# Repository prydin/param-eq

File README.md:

# Parametric EQ to DSP Playground

This project started as a focused experiment: build a practical, hardware-controlled parametric equalizer.
Along the way it grew into something broader: a general-purpose DSP platform for real-time audio processing,
instrumentation, and UI experiments.

What began as "just three EQ bands" now includes filter control, combined response visualization,
VU metering, spectrum visualization, and a register-based control/data protocol between two MCUs.

## Project Story

The original goal was simple:

1. Build a hands-on parametric EQ with physical controls.
2. Show the selected filter behavior and resulting response in real time.
3. Keep the software and hardware open enough to keep evolving.

That third point changed everything. Once the DSP core and UI link were stable, it became obvious that
the architecture could do far more than EQ alone. The codebase now behaves more like a modular DSP
workbench than a single-purpose effect.

## Architecture

The system uses two processors, each doing the job it is best at.

### Teensy 4.1: Audio DSP Engine

- Handles real-time signal processing.
- Computes filter behavior and response data.
- Publishes metering and spectrum data.
- Maintains the parameter/register state that the UI consumes.

Why Teensy 4.1:

- Cortex-M7 performance is excellent for this class of project.
- Floating-point math is fast enough to keep filter code readable and robust.
- Great ecosystem for embedded audio prototyping.

### ESP32 CYD: UI Processor

The UI runs on a CYD (Cheap Yellow Display), which is an ESP32-based board with an integrated TFT.

- Renders LVGL-based UI modes.
- Reads user input from rotary encoders/buttons.
- Displays EQ response, VU, and spectrum information.
- Exchanges register updates with the Teensy via I2C.

### Interconnect: Register-Based I2C Protocol

Communication between DSP and UI uses compact register messages over I2C.

- Control parameters and mode changes flow from UI-side interactions.
- DSP publishes status, levels, and spectrum bins back to UI.
- Commit-style register updates keep state transitions predictable.

## UI Modes

The UI currently provides three main modes, each optimized for a different use case.

### 1) Detailed EQ Mode

Purpose: precise tuning and analysis.

- Displays selected filter response and optional combined response.
- Shows active filter type and selected filter band.
- Shows numeric parameter values including frequency, gain, Q, sample rate, and level settings.
- Intended for surgical parameter work.

### 2) Simple Meter Mode

Purpose: quick operating view.

- Large, easy-to-read core values.
- Stereo VU metering with ballistic behavior and peak hold.
- Designed for "use while listening" rather than deep editing.

### 3) Spectrum Analyzer Mode

Purpose: visualize real-time spectral behavior.

- Real-time spectrum bars with smoothing and peak hold.
- Log-style frequency scale and supplemental operating info.
- Useful for spotting trends, resonances, and level distribution.

### Filter Parameter Popup Overlay

When operating in Simple or Spectrum mode, parameter changes can trigger a framed popup showing key
filter settings (band, type, frequency, gain, and Q). The popup auto-hides after inactivity, and can
be gated by user-input state so remote/background updates do not constantly interrupt the view.

## Current Scope

- Multi-band parametric EQ control.
- Low shelf, high shelf, and peak filter workflows.
- Dual-MCU DSP/UI split with robust register transport.
- Multiple operator-focused UI modes.
- Real-time VU and spectrum visualization.

## Where It Is Heading

Long term, the plan is to fold this work into a DAC/DSP/preamplifier build.
This repository is the proving ground for that hardware/software stack.

## Acknowledgements

Big thanks to the diyAudio.com community.

Many design choices, implementation refinements, and troubleshooting ideas were inspired by the
knowledge shared by diyAudio members. The project benefited directly from their practical guidance,
experience, and generosity in public discussion threads.

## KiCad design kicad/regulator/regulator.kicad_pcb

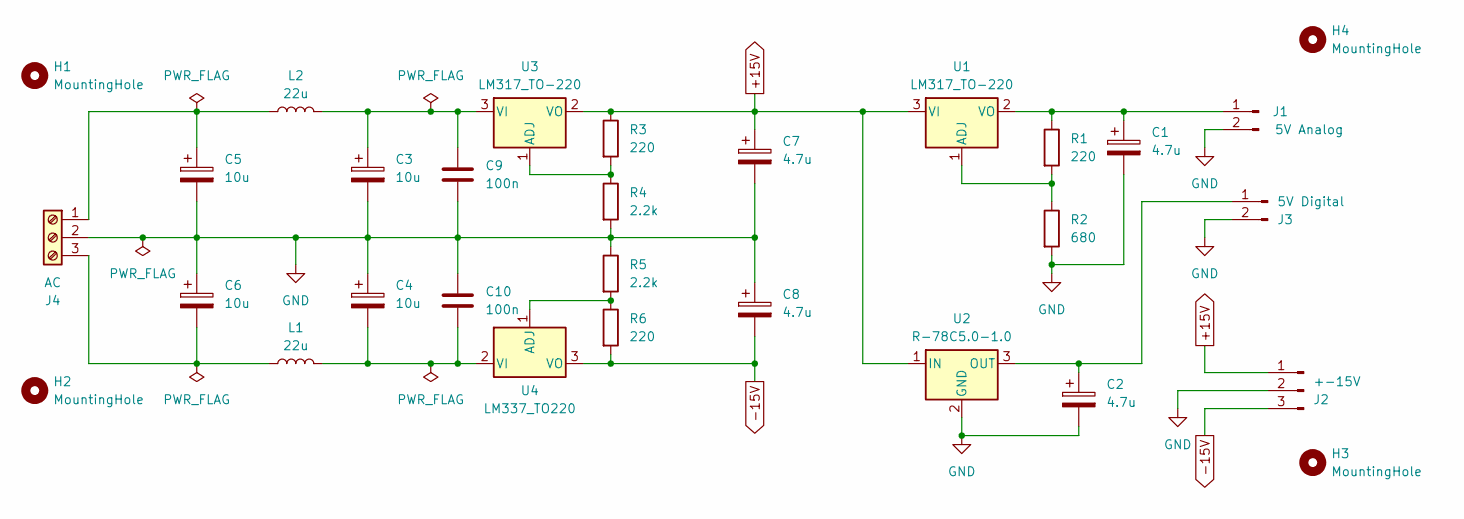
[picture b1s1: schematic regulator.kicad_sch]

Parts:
C1, C2, C7, C8: 4.7u; CP_Radial_D4.0mm_P1.50mm
C3, C4, C5, C6: 10u; CP_Radial_D4.0mm_P1.50mm
C9, C10: 100n; C_Disc_D3.8mm_W2.6mm_P2.50mm
H1, H2, H3, H4: MountingHole; MountingHole_3.2mm_M3
J1: 5V Analog; JST_PH_B2B-PH-K_1x02_P2.00mm_Vertical
J2: +-15V; JST_PH_B3B-PH-K_1x03_P2.00mm_Vertical
J3: 5V Digital; JST_PH_B2B-PH-K_1x02_P2.00mm_Vertical
J4: AC; TerminalBlock_Phoenix_MPT-0,5-3-2.54_1x03_P2.54mm_Horizontal
L1, L2: 22u; L_Toroid_Vertical_L17.8mm_W8.1mm_P7.62mm_Bourns_5700
R1, R3, R6: 220; R_Axial_DIN0204_L3.6mm_D1.6mm_P7.62mm_Horizontal
R2: 680; R_Axial_DIN0204_L3.6mm_D1.6mm_P7.62mm_Horizontal
R4, R5: 2.2k; R_Axial_DIN0204_L3.6mm_D1.6mm_P7.62mm_Horizontal
U1, U3: LM317_TO-220; TO-220-3_Vertical
U2: R-78C5.0-1.0; Converter_DCDC_RECOM_R-78E-0.5_THT
U4: LM337_TO220; TO-220-3_Vertical

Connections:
+15V: C7.1, J2.1, R3.1, U1.3 (VI), U2.1 (IN), U3.2 (VO)
-15V: C8.2, J2.3, R6.2, U4.3 (VO)
GND: C1.2, C2.2, C3.2, C4.1, C5.2, C6.1, C7.2, C8.1, C9.2, C10.1, J1.2, J2.2, J3.2, J4.2, R2.2, R4.2, R5.1, U2.2 (GND)
unnamed: C1.1, J1.1, R1.1, U1.2 (VO)
unnamed: C2.1, J3.1, U2.3 (OUT)
unnamed: C5.1, J4.1, L2.1
unnamed: C6.2, J4.3, L1.1
unnamed: R1.2, R2.1, U1.1 (ADJ)
unnamed: R3.2, R4.1, U3.1 (ADJ)
unnamed: C3.1, C9.1, L2.2, U3.3 (VI)
unnamed: R5.2, R6.1, U4.1 (ADJ)
unnamed: C4.2, C10.2, L1.2, U4.2 (VI)

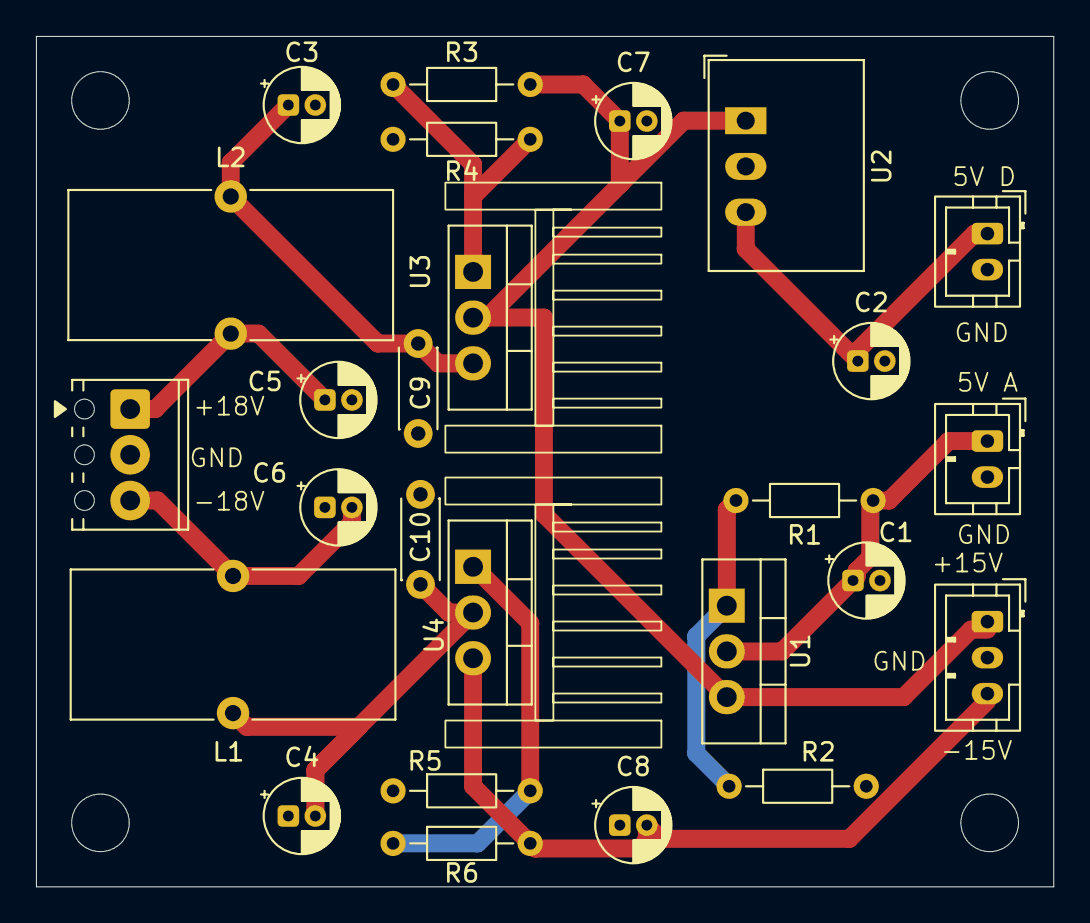
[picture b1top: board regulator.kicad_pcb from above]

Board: 2 copper layers, 56.5 x 47.2 mm, 30 parts (0 on the bottom side), 12 nets.

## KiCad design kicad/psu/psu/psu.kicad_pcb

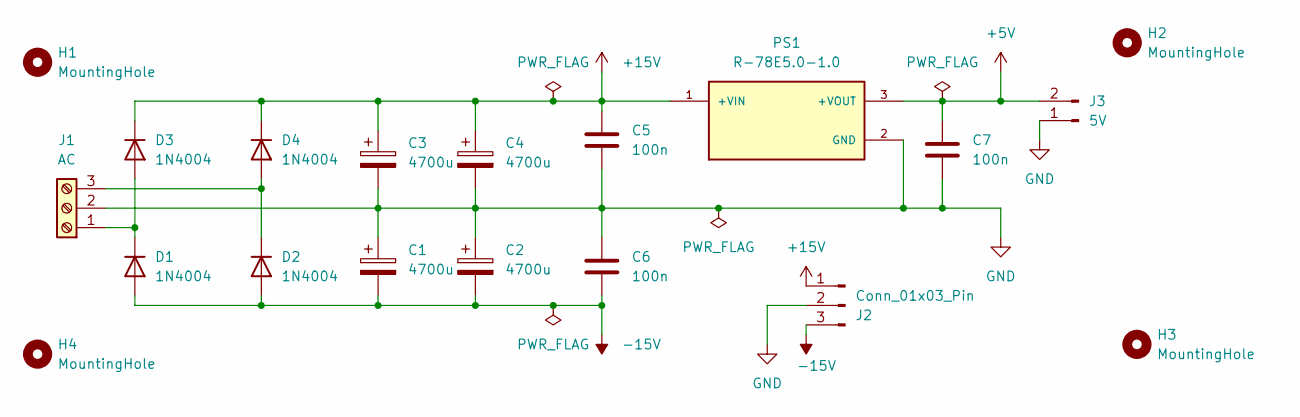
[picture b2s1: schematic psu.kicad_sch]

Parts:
C1, C2, C3, C4: 4700u; CP_Radial_D16.0mm_P7.50mm
C5, C6, C7: 100n; C_Disc_D5.0mm_W2.5mm_P5.00mm
D1, D2, D3, D4: 1N4004; D_DO-41_SOD81_P10.16mm_Horizontal
H1, H2, H3, H4: MountingHole; MountingHole_3.2mm_M3
J1: AC; TerminalBlock_Phoenix_MPT-0,5-3-2.54_1x03_P2.54mm_Horizontal
J2: Conn_01x03_Pin; JST_PH_B3B-PH-K_1x03_P2.00mm_Vertical
J3: 5V; JST_PH_B2B-PH-K_1x02_P2.00mm_Vertical
PS1: R-78E5.0-1.0; CONV_R-78E5.0-1.0; PARTREV 6

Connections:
+5V: C7.1, J3.2, PS1.3 (+VOUT)
+15V: C3.1, C4.1, C5.1, D3.1 (K), D4.1 (K), J2.1, PS1.1 (+VIN)
-15V: C1.2, C2.2, C6.2, D1.2 (A), D2.2 (A), J2.3
GND: C1.1, C2.1, C3.2, C4.2, C5.2, C6.1, C7.2, J1.2, J2.2, J3.1, PS1.2 (GND)
unnamed: D1.1 (K), D3.2 (A), J1.1
unnamed: D2.1 (K), D4.2 (A), J1.3

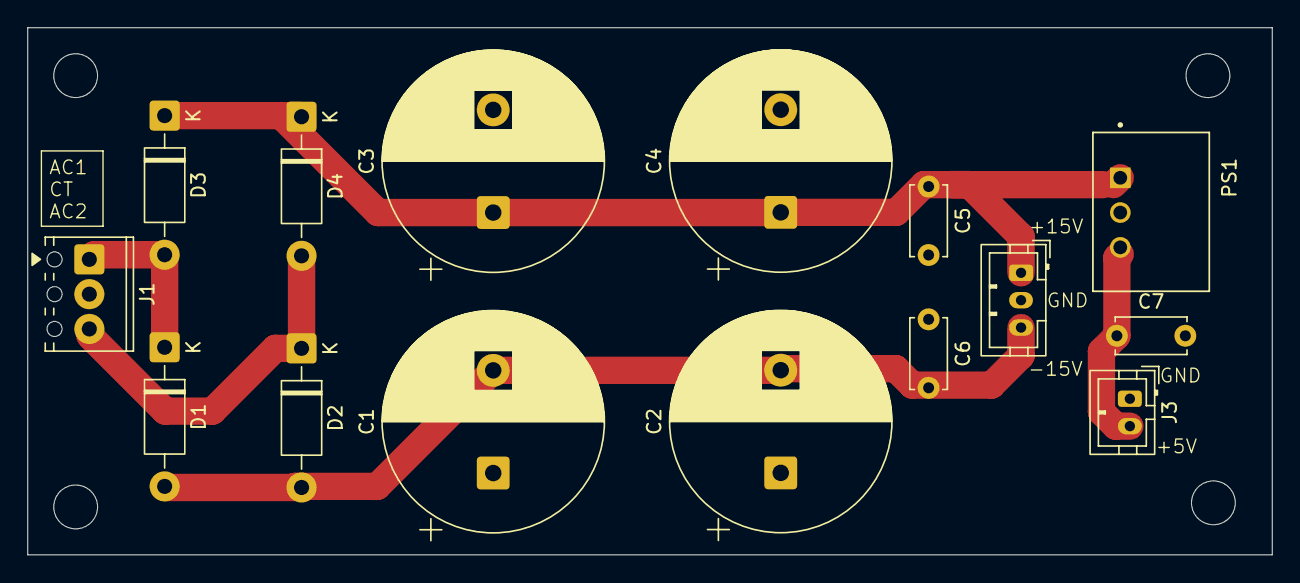
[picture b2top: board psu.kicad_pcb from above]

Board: 2 copper layers, 90.9 x 38.5 mm, 19 parts (0 on the bottom side), 6 nets.

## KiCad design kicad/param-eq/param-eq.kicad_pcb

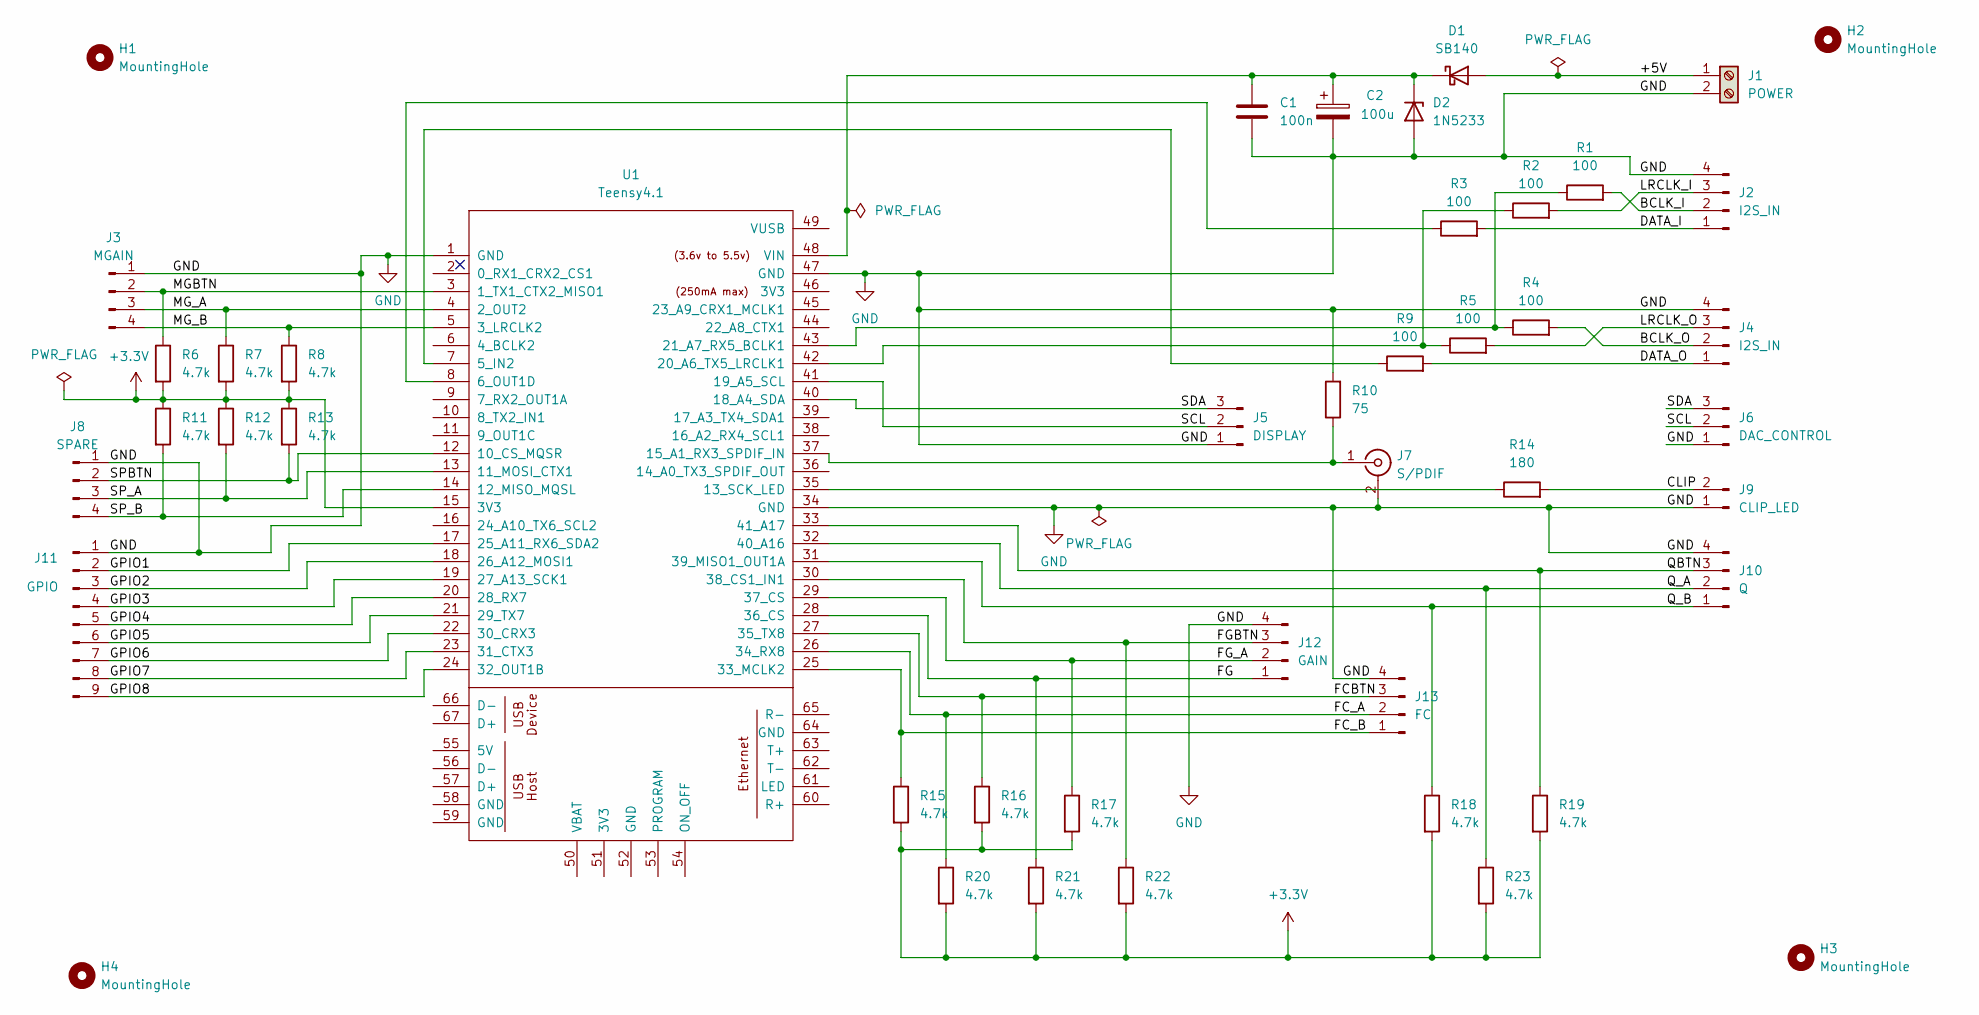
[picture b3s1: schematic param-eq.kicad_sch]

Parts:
C1: 100n; C_Rect_L7.2mm_W3.0mm_P5.00mm_FKS2_FKP2_MKS2_MKP2_HandSolder
C2: 100u; CP_Radial_D8.0mm_P5.00mm
D1: SB140; D_DO-41_SOD81_P10.16mm_Horizontal
D2: 1N5233; D_DO-41_SOD81_P10.16mm_Horizontal
H1, H2, H3, H4: MountingHole; MountingHole_3.2mm_M3
J1: POWER; TerminalBlock_4Ucon_1x02_P3.50mm_Horizontal
J2, J4: I2S_IN; JST_PH_B4B-PH-K_1x04_P2.00mm_Vertical
J3: MGAIN; JST_PH_B4B-PH-K_1x04_P2.00mm_Vertical
J5: DISPLAY; JST_PH_B3B-PH-K_1x03_P2.00mm_Vertical
J6: DAC_CONTROL; JST_PH_B3B-PH-K_1x03_P2.00mm_Vertical
J7: S/PDIF; TestPoint_2Pads_Pitch2.54mm_Drill0.8mm
J8: SPARE; JST_PH_B4B-PH-K_1x04_P2.00mm_Vertical
J9: CLIP_LED; JST_PH_B2B-PH-K_1x02_P2.00mm_Vertical
J10: Q; JST_PH_B4B-PH-K_1x04_P2.00mm_Vertical
J11: GPIO; PinHeader_1x09_P2.54mm_Vertical
J12: GAIN; JST_PH_B4B-PH-K_1x04_P2.00mm_Vertical
J13: FC; JST_PH_B4B-PH-K_1x04_P2.00mm_Vertical
R1, R2, R3, R4, R5, R9: 100; R_Axial_DIN0204_L3.6mm_D1.6mm_P2.54mm_Vertical
R6, R7, R8, R11, R12, R13, R15, R16, R17, R18, R19, R20, R21, R22, R23: 4.7k; R_Axial_DIN0204_L3.6mm_D1.6mm_P7.62mm_Horizontal_HandSolder
R10: 75; R_Axial_DIN0204_L3.6mm_D1.6mm_P7.62mm_Horizontal_HandSolder
R14: 180; R_Axial_DIN0204_L3.6mm_D1.6mm_P7.62mm_Horizontal_HandSolder
U1: Teensy4.1; Teensy41

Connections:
+3.3V: R6.2, R7.2, R8.2, R11.1, R12.1, R13.1, R15.2, R16.2, R17.2, R18.2, R19.2, R20.2, R21.2, R22.2, R23.2, U1.15 (3V3)
/+5V: D1.2 (A), J1.1
/BCLK_I: J2.2, R1.2
/BCLK_O: J4.2, R4.2
/CLIP: J9.2, R14.2
/DATA_I: J2.1, R3.2
/DATA_O: J4.1, R9.2
/FCBTN: J13.3, R16.1, U1.27 (35_TX8)
/FC_A: J13.2, R20.1, U1.26 (34_RX8)
/FC_B: J13.1, R15.1, U1.25 (33_MCLK2)
/FG: J12.1, R21.1, U1.28 (36_CS)
/FGBTN: J12.3, R22.1, U1.30 (38_CS1_IN1)
/FG_A: J12.2, R17.1, U1.29 (37_CS)
/GPIO1: J11.2, U1.17 (25_A11_RX6_SDA2)
/GPIO2: J11.3, U1.18 (26_A12_MOSI1)
/GPIO3: J11.4, U1.19 (27_A13_SCK1)
/GPIO4: J11.5, U1.20 (28_RX7)
/GPIO5: J11.6, U1.21 (29_TX7)
/GPIO6: J11.7, U1.22 (30_CRX3)
/GPIO7: J11.8, U1.23 (31_CTX3)
/GPIO8: J11.9, U1.24 (32_OUT1B)
/LRCLK_I: J2.3, R2.2
/LRCLK_O: J4.3, R5.2
/MGBTN: J3.2, R6.1, U1.3 (1_TX1_CTX2_MISO1)
/MG_A: J3.3, R7.1, U1.4 (2_OUT2)
/MG_B: J3.4, R8.1, U1.5 (3_LRCLK2)
/QBTN: J10.3, R19.1, U1.33 (41_A17)
/Q_A: J10.2, R23.1, U1.32 (40_A16)
/Q_B: J10.1, R18.1, U1.31 (39_MISO1_OUT1A)
/SCL: J5.2, J6.2, U1.41 (19_A5_SCL)
/SDA: J5.3, J6.3, U1.40 (18_A4_SDA)
/SPBTN: J8.2, R13.2, U1.12 (10_CS_MQSR)
/SP_A: J8.3, R12.2, U1.13 (11_MOSI_CTX1)
/SP_B: J8.4, R11.2, U1.14 (12_MISO_MQSL)
GND: C1.2, C2.2, D2.2 (A), J1.2, J2.4, J3.1, J4.4, J5.1, J6.1, J7.2 (Ext), J8.1, J9.1, J10.4, J11.1, J12.4, J13.4, R10.2, U1.1 (GND), U1.34 (GND), U1.47 (GND)
unnamed: C1.1, C2.1, D1.1 (K), D2.1 (K), U1.48 (VIN)
unnamed: J7.1 (In), R10.1, U1.37 (15_A1_RX3_SPDIF_IN)
unnamed: R9.1, U1.7 (5_IN2)
unnamed: R3.1, U1.8 (6_OUT1D)
unnamed: R14.1, U1.35 (13_SCK_LED)
unnamed: R2.1, R5.1, U1.42 (20_A6_TX5_LRCLK1)
unnamed: R1.1, R4.1, U1.43 (21_A7_RX5_BCLK1)

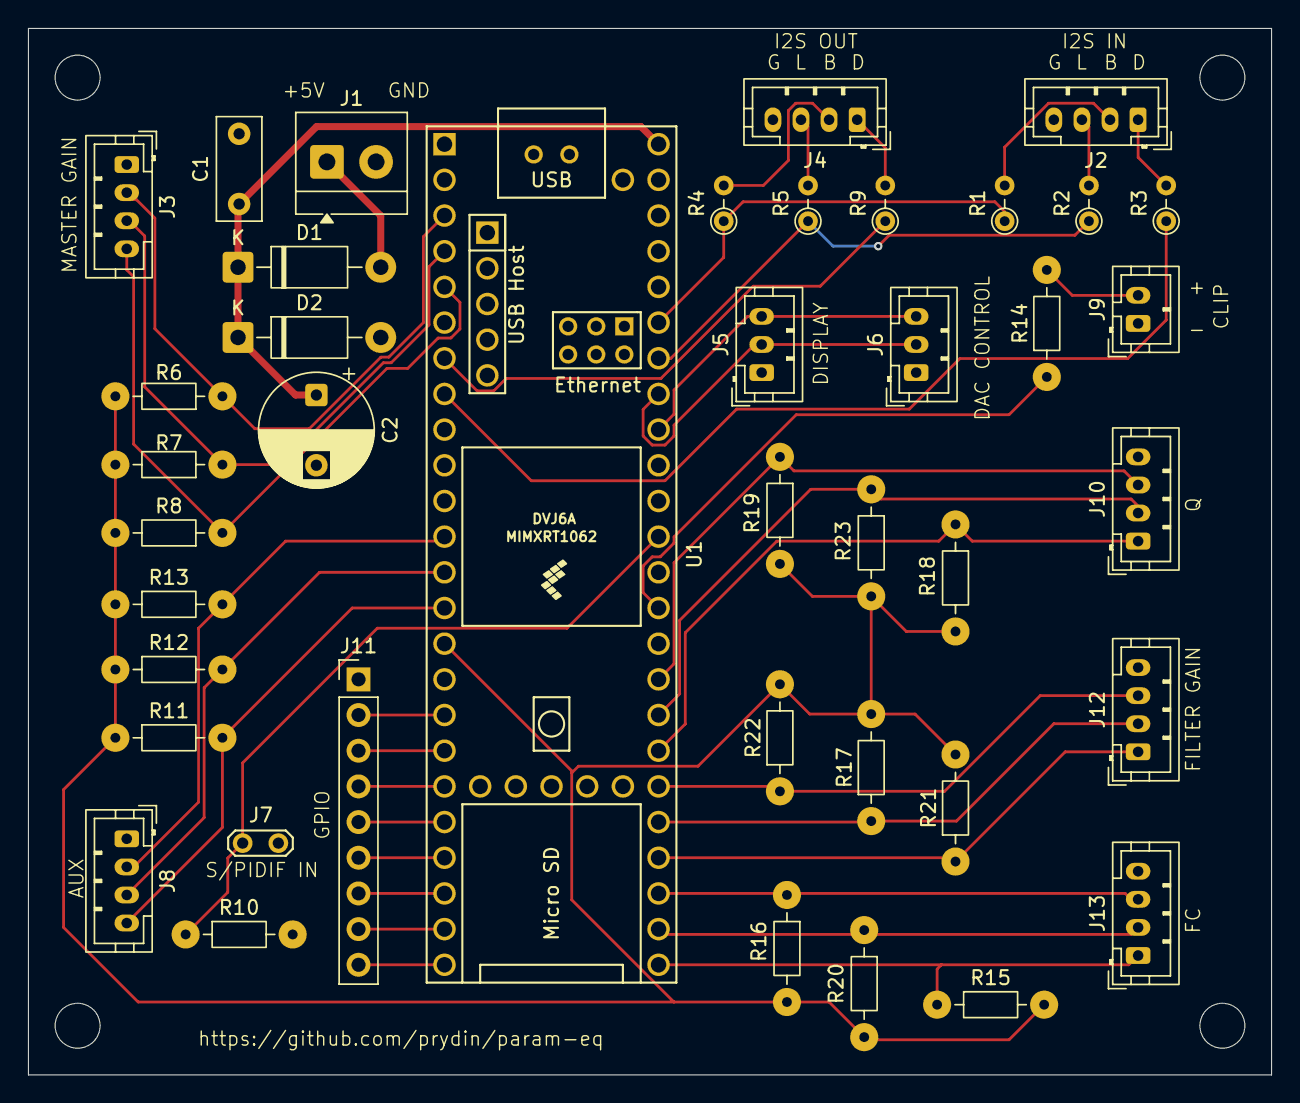
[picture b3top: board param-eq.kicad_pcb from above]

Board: 2 copper layers, 88.5 x 74.5 mm, 45 parts (0 on the bottom side), 42 nets.

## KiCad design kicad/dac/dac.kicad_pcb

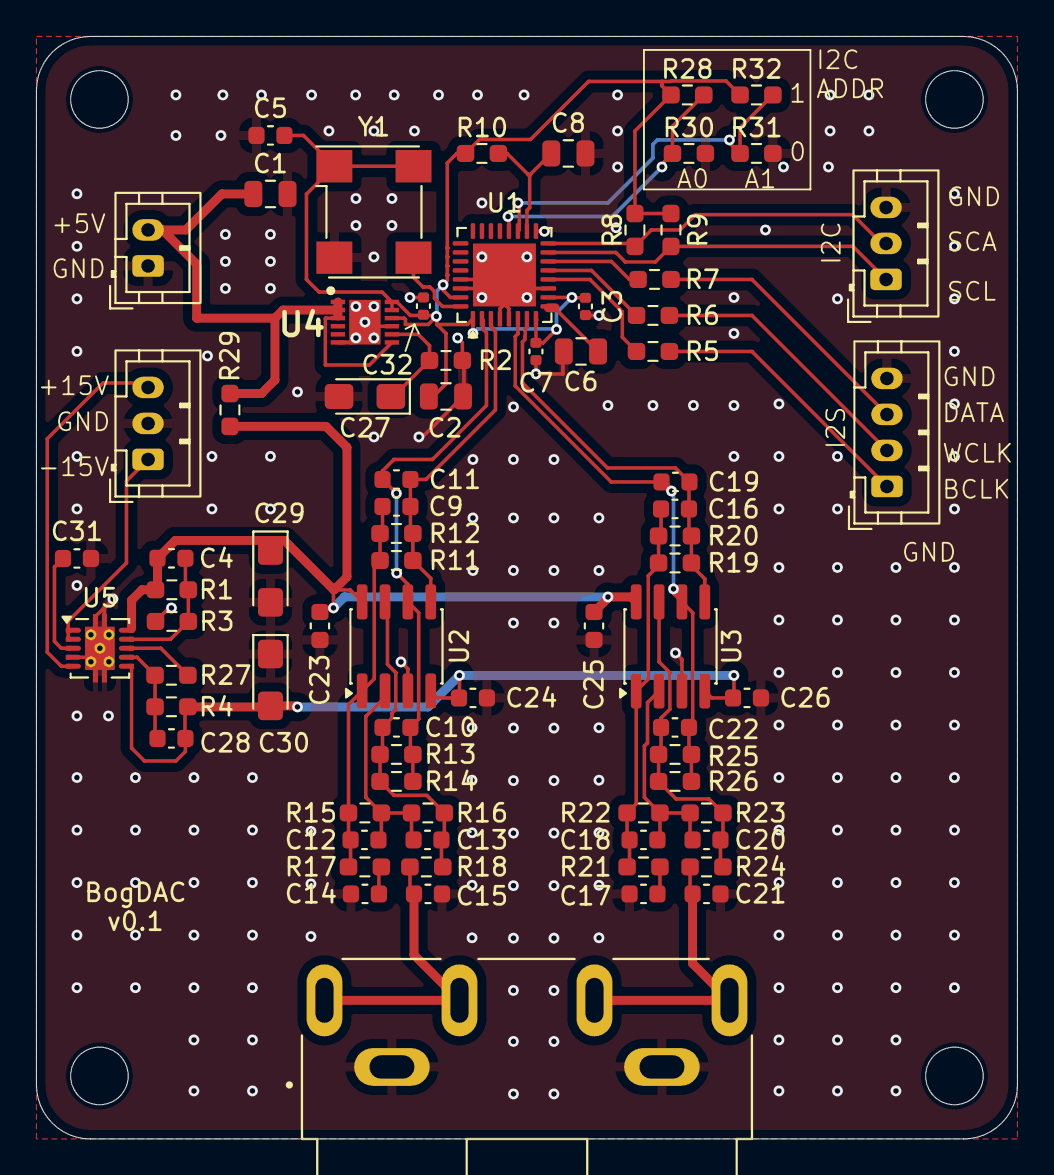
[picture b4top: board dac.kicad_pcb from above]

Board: 4 copper layers, 54.5 x 61.2 mm, 79 parts (0 on the bottom side), 39 nets.

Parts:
C1, C2, C6, C8: 10u; C_0805_2012Metric
C3, C7, C32: 100n; C_0402_1005Metric
C4, C28, C31: 10n; C_0603_1608Metric
C5, C23, C24, C25, C26: 100n; C_0603_1608Metric
C9, C10, C16, C22: 510p; C_0603_1608Metric
C11, C19: 1p; C_0603_1608Metric
C12, C13, C18, C20: 10p; C_0603_1608Metric
C14, C15, C17, C21: 2.2n; C_0603_1608Metric
C27, C29, C30: 22u; CP_EIA-3216-10_Kemet-I_HandSolder
H1, H2, H3, H4: MountingHole; MountingHole_3.2mm_M3
J1: I2S; JST_PH_B3B-PH-K_1x03_P2.00mm_Vertical
J2: I2S; JST_PH_B4B-PH-K_1x04_P2.00mm_Vertical
J3: ANALOG PWR; JST_PH_B3B-PH-K_1x03_P2.00mm_Vertical
J4: 5V; JST_PH_B2B-PH-K_1x02_P2.00mm_Vertical
J5: AUDIO OUT; SWITCHCRAFT_PJRAN2X1U01AUX
R1: 90.9k; R_0603_1608Metric_Pad0.98x0.95mm_HandSolder
R2: 33.2k; R_0603_1608Metric_Pad0.98x0.95mm_HandSolder
R3, R27: 10k; R_0603_1608Metric_Pad0.98x0.95mm_HandSolder
R4: 100k; R_0603_1608Metric_Pad0.98x0.95mm_HandSolder
R5, R6, R7: 50; R_0603_1608Metric_Pad0.98x0.95mm_HandSolder
R8, R9, R15, R16, R22, R23: 4.7k; R_0603_1608Metric_Pad0.98x0.95mm_HandSolder
R10: 47k; R_0603_1608Metric_Pad0.98x0.95mm_HandSolder
R11, R12, R13, R14, R19, R20, R25, R26: 3.6k; R_0603_1608Metric_Pad0.98x0.95mm_HandSolder
R17, R18, R21, R24: 140; R_0603_1608Metric_Pad0.98x0.95mm_HandSolder
R28, R29, R30, R31, R32: 0; R_0603_1608Metric_Pad0.98x0.95mm_HandSolder
U1: ES9039Q2M; UFQFPN-32-1EP_5x5mm_P0.5mm_EP3.5x3.5mm
U2, U3: OPA1612AxD; SOIC-8_3.9x4.9mm_P1.27mm
U4: LT3046ATC+; SON45P300X300X80-13N-D
U5: TPS7A39; Texas_S-PVSON-N10_ThermalVias
Y1: CE3391-49.152; Oscillator_SMD_Diodes_FN-4Pin_7.0x5.0mm

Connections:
+3.3V: C2.1, C3.1, C5.1, C7.1, C32.1, R8.1, R9.1, R10.1, R28.1, R32.1, U1.1 (AVCC_DAC1), U1.8 (AVCC_DAC2), U1.10 (AVDD), U1.31 (VCCA), U4.10 (OUTS), U4.11 (OUT_1), U4.12 (OUT_2), Y1.1 (OE), Y1.4 (VDD)
+5V: C1.1, J4.2, R29.2, U4.1 (IN_1), U4.2 (IN_2), U4.3 (EN/UV), U4.7 (PGFB)
+12V: C4.1, C23.2, C25.2, C29.1, R1.1, R29.1, U2.8 (V+), U3.8 (V+), U5.10 (OUTP)
-12V: C24.1, C26.1, C28.2, C30.2, R4.2, U2.4 (V-), U3.4 (V-), U5.6 (OUTN)
/+15V: J3.1, U5.1 (INP), U5.2 (EN)
/-15V: J3.3, U5.5 (INN)
/BCLK: J2.1, R5.2
/DATA: J2.3, R7.2
/SCA: J1.2, R8.2, U1.16 (SCA)
/SCL: J1.1, R9.2, U1.15 (SCL)
/WCLK: J2.2, R6.2
DAC1: C9.1, C11.2, R11.1, R12.1, U1.3 (DAC1), U2.5 (+)
DAC1B: C10.1, C11.1, R13.1, R14.1, U1.2 (DAC1B), U2.6 (-)
DAC2: C16.1, C19.2, R19.1, R20.1, U1.7 (DAC2), U3.5 (+)
DAC2B: C19.1, C22.1, R25.1, R26.1, U1.6 (DAC2B), U3.6 (-)
GND: C1.2, C2.2, C3.2, C5.2, C6.2, C7.2, C8.2, C14.1, C15.1, C17.1, C21.1, C23.1, C24.2, C25.1, C26.2, C27.2, C29.2, C30.1, C31.2, C32.2, J1.3, J2.4, J3.2, J4.1, J5.1_A, J5.1_B, R2.2, R3.1, R30.2, R31.2, U1.4 (AGND_DAC1), U1.5 (AGND_DAC2), U1.11 (GND), U1.17 (RT1), U1.29 (MODE), U1.30 (GND), U1.33 (PAD), U2.3 (+), U3.3 (+), U4.6 (ILIM), U4.9 (GND_1), U4.13 (GND_2), U5.4 (GND), U5.11 (GND), Y1.2 (GND)
unnamed: C10.2, C13.1, R13.2, R14.2, R16.1, R18.1, U2.7
unnamed: C9.2, C12.2, R11.2, R12.2, R15.2, R17.1, U2.1
unnamed: C14.2, R17.2
unnamed: C15.2, J5.2_A, J5.3_A, R18.2
unnamed: C16.2, C18.2, R19.2, R20.2, R21.1, R22.2, U3.1
unnamed: C17.2, R21.2
unnamed: C20.1, C22.2, R23.1, R24.1, R25.2, R26.2, U3.7
unnamed: C21.2, J5.2_B, J5.3_B, R24.2
unnamed: R28.2, R30.1, U1.20 (ADDR0)
unnamed: R31.1, R32.2, U1.19 (ADDR1)
unnamed: C8.1, R10.2, U1.18 (CHIP_EN)
unnamed: R6.1, U1.13 (DATA1)
unnamed: R7.1, U1.14 (DATA2)
unnamed: R5.1, U1.12 (DATA_CLK)
unnamed: C6.1, U1.9 (DVDD)
unnamed: U1.32 (MCLK), Y1.3 (OUT)
unnamed: C12.1, C13.2, R15.1, R16.2, U2.2 (-)
unnamed: C18.1, C20.2, R22.1, R23.2, U3.2 (-)
unnamed: C27.1, R2.1, U4.8 (SET)
unnamed: R27.2, U5.8 (BUF)
unnamed: C28.1, R4.1, R27.1, U5.7 (FBN)
unnamed: C4.2, R1.2, R3.2, U5.9 (FBP)
unnamed: C31.1, U5.3 (NR/SS)

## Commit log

2025-12-14 Display stuff
2025-12-21 Create README.md for parametric equalizer project
    Added initial README with project overview and details.
2025-12-21 Added images
2025-12-21 Add UI images to README
    Added images to README for UI representation.
2026-01-03 Logarithmic fq scale
2026-01-04 Master gain
2026-01-04 Create Teensy4i2s
2026-01-06 Doubles phase 1
2026-02-16 Removed submodule
2026-02-17 Added DAC re-initialization
2026-03-19 New UI
2026-03-22 Added USB audio
2026-03-22 Enhance README with images and DSP module details
    Updated README.md to include new images and details about the DSP and UI modules.
2026-03-22 Renamed files
2026-03-23 Improved sample rate detection.
2026-03-27 Revert "Merge branch 'main' of https://github.com/prydin/param-eq"
    This reverts commit 389628c2baba959bef1beb1be98a9c41f163846e, reversing
    changes made to 7efa158129df0e81abc05ebdd55c449f5cfdd2da.
2026-03-27 Control refactoring
2026-03-29 FFT Display
2026-03-29 Spectrum analyzer
2026-03-29 CQT experiment
2026-03-30 Removed dual channel FFT
2026-03-30 Spectrum improvments
2026-04-01 UI fine tuning
2026-04-02 Filter parameter popup
2026-04-03 Display update improvments
2026-04-03 UI and visualization adjustments
2026-04-12 Replace old images with new visuals in README
    Updated images in README to include new visuals.
